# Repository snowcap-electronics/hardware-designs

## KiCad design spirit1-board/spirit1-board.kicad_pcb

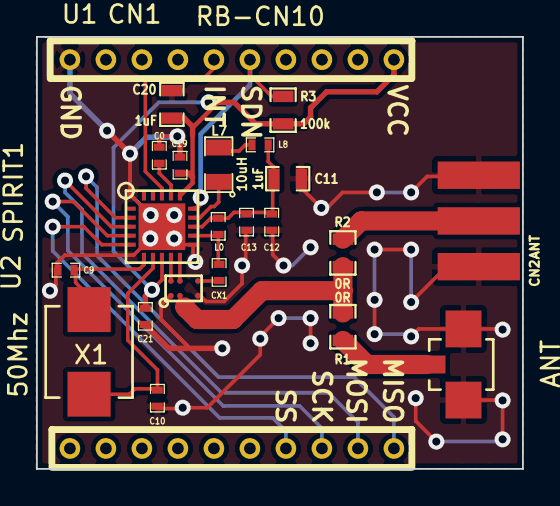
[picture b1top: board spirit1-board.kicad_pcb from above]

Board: 2 copper layers, 27.0 x 24.0 mm, 22 parts (0 on the bottom side), 21 nets.

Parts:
C0, C12: 100nF; SM0402_c
C9: 12pF; SM0402_c
C10: 10pF; SM0402_c
C11, C20: 1uF; SM0603_Capa
C13: 330pF; SM0402_c
C19: 10nF; SM0402_c
C21: 100pF; SM0402_c
CN1: RB-CN10; RB_CN10_2mm
CN2: ANT; RF_SMA
CN3: ANT; U.FL-R-SMT_01
CX1: C; SM0402_c
L0: 150nH; SM0402
L7: 10uH; SM0805
L8: 62nH; SM0402
R1, R2: 0R; SM0603_Resistor
R3: 100k; SM0603_Resistor
U1: SPIRIT1; SPIRIT1_QFN20
U2: BALF-SPI-02D3; BALF_SPI_02D3
X1: 50Mhz; CRYSTAL-ABM3-50.000MHZ-D2Y-F-T

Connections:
/50ohm: R1.2, R2.1, U2.B1
GND: C0.2, C9.2, C10.2, C11.2, C12.2, C13.2, C19.2, C20.2, C21.2, CN1.10, CN2.2, CN3.2, U1.11, U1.21, U2.A1, U2.C1
unnamed: CN1.11, U1.2
unnamed: CN1.12, U1.3
unnamed: CN1.13, U1.4
unnamed: CN1.14, U1.5
unnamed: C0.1, U1.17
unnamed: CN1.5, R3.2, U1.15
unnamed: CN1.6, U1.18
unnamed: CN3.1, R1.1
unnamed: CN2.1, R2.2
unnamed: C11.1, C12.1, C13.1, L0.2, L8.2, U1.13
unnamed: L7.2, L8.1
unnamed: C9.1, U1.6, X1.1
unnamed: C10.1, U1.7, X1.2
unnamed: L7.1, U1.14
unnamed: U1.9, U2.A2
unnamed: U1.10, U2.B2
unnamed: CX1.1, L0.1, U1.12
unnamed: CX1.2, U2.C2
VCC: C19.1, C20.1, C21.1, CN1.1, R3.1, U1.8, U1.16

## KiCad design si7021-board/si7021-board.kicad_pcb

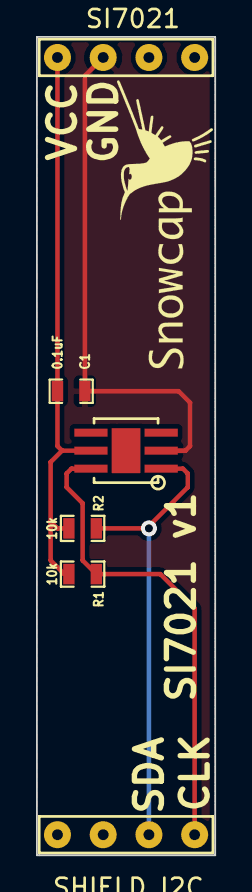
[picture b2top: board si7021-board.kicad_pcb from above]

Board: 2 copper layers, 9.9 x 45.5 mm, 5 parts (0 on the bottom side), 4 nets.

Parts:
C1: 0.1uF; SM0603_Capa
R1, R2: 10k; SM0603_Resistor
U1: SHIELD_I2C
U2: SI7021

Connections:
GND: C1.2, U1.2, U2.2
unnamed: R1.2, U1.8, U2.6
unnamed: R2.2, U1.7, U2.1
VCC: C1.1, R1.1, R2.1, U1.1, U2.5

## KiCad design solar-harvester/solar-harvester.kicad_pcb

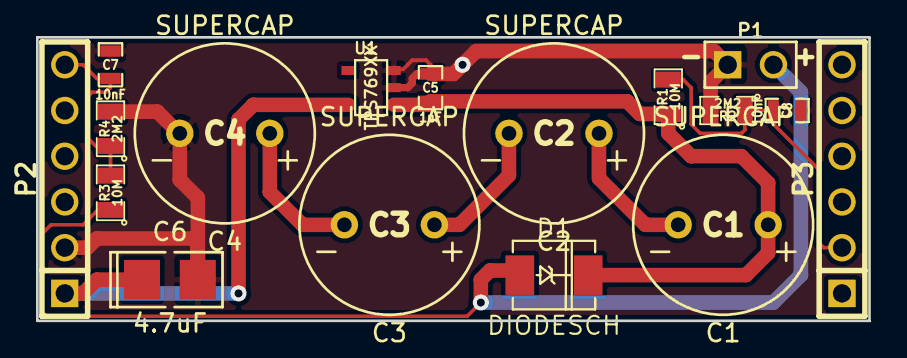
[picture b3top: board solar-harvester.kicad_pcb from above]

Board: 2 copper layers, 46.2 x 15.7 mm, 17 parts (0 on the bottom side), 9 nets.

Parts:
C1, C2, C3, C4: SUPERCAP; SUPERCAP_ESHSR-0010C0-002R7
C5: 1uF; SM0603_Capa
C6: 4.7uF; SM1411_POL
C7, C8: 10nF; SM0603_Capa
D1: DIODESCH; DO-214AC(SMA)
P1: CONN_2; PIN_ARRAY_2X1
P2, P3: CONN_6; PIN_ARRAY-6X1
R1, R3: 10M; SM0805
R2, R4: 2M2; SM0805
U1: TPS769XX; SOT23-5

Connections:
/V_MEASURE1: C7.1, P2.6, R3.2, R4.1
/V_MEASURE2: C8.1, P3.2, R1.2, R2.1
GND: C4.2, C5.2, C6.2, C7.2, C8.2, P1.1, P2.2, R2.2, R4.2, U1.2, U1.3
unnamed: C2.2, C3.1
unnamed: D1.1, P1.2, R3.1
unnamed: C6.1, P2.1, U1.5
unnamed: C1.2, C2.1
unnamed: C1.1, C5.1, D1.2, R1.1, U1.1
unnamed: C3.2, C4.1

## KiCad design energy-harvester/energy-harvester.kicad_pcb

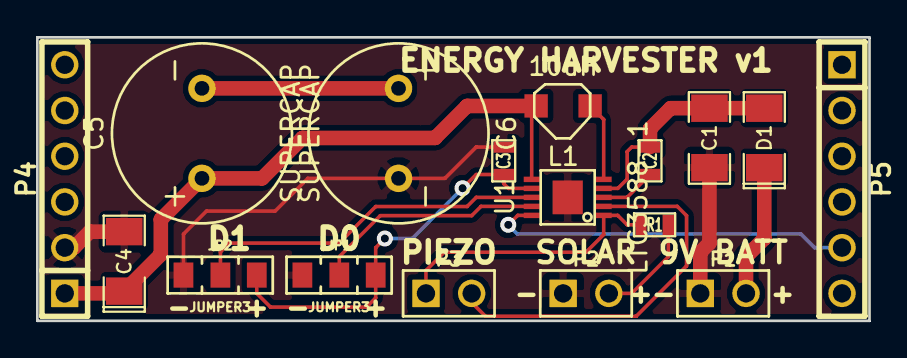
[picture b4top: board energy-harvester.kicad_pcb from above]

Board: 2 copper layers, 46.2 x 15.7 mm, 17 parts (0 on the bottom side), 14 nets.

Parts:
C1: 100uF; SM1206
C2: 1uF; SM0603
C3: 4.7uF; SM0603
C4: 10uF; SM1206POL
C5, C6: SUPERCAP; SUPERCAP_ESHSR-0010C0-002R7
D1: DIODESCH; SM1206POL
JP1, JP2: JUMPER3; SM0805_JUMPER3
L1: 10uH; INDUCTOR-CDRH2D18-LD
P1, P2, P3: CONN_2; PIN_ARRAY_2X1
P4, P5: CONN_6; PIN_ARRAY-6X1
R1: 300R; SM0603
U1: LTC3588-1; LTC3588-1-MSOP10

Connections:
/PGOOD: P5.5, U1.10
/VIN2: C3.1, JP1.3, JP2.3, U1.7
GND: C1.2, C3.2, C4.2, C6.2, JP1.1, JP2.1, P1.1, P2.1, P4.2, U1.11
unnamed: P3.1, R1.2, U1.1
unnamed: P3.2, U1.2
unnamed: JP2.2, U1.8
unnamed: C5.2, C6.1
unnamed: JP1.2, U1.9
unnamed: D1.1, P1.2
unnamed: C2.2, U1.3
unnamed: P2.2, R1.1
unnamed: L1.1, U1.5
unnamed: C1.1, C2.1, D1.2, U1.4
VCC: C4.1, C5.1, L1.2, P4.1, U1.6

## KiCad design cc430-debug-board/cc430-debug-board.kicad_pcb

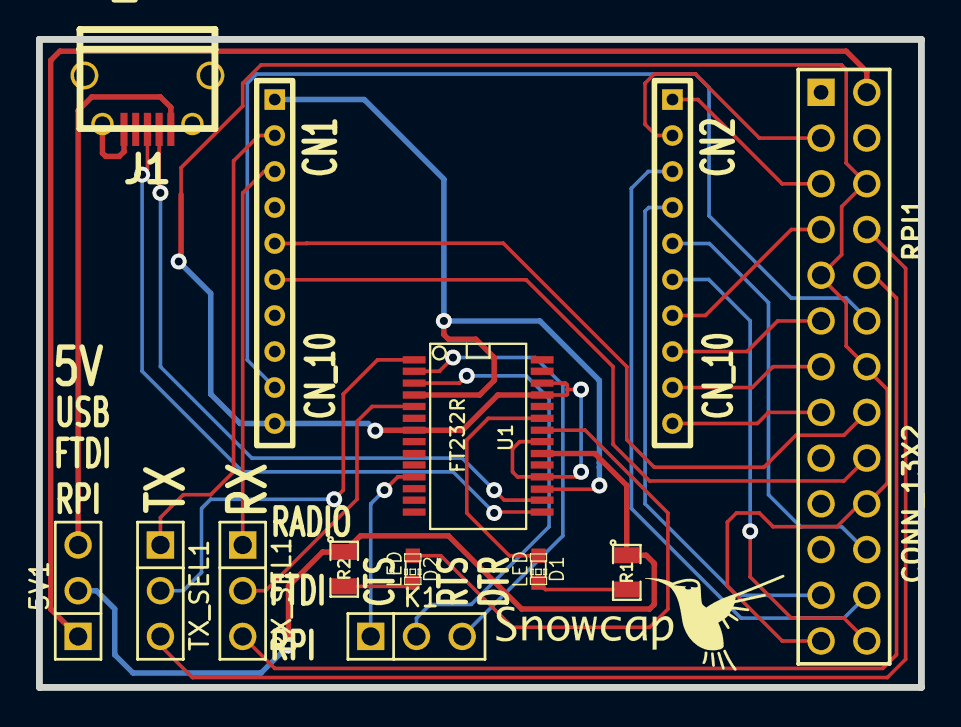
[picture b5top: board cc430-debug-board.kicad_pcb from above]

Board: 2 copper layers, 49.0 x 36.0 mm, 13 parts (0 on the bottom side), 33 nets.

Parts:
5V1: CN_3; PIN_ARRAY_3X1
CN1, CN2: CN_10; CONN-10-2MM
D1, D2: LED; LED-0603
J1: USB_MICRO; USB_MICRO_10118194-0001LF
K1: CONN_3; PIN_ARRAY_3X1
R1, R2: 500R; SM0805
RPI1: CONN_13X2; pin_array_13x2
RX_SEL1: CN_3; PIN_ARRAY_3X1
TX_SEL1: CN_3; PIN_ARRAY_3X1
U1: FT232R; SSOP28

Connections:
+3.3V: CN1.1, U1.4, U1.17
+5V: 5V1.2, R1.1, R2.1, U1.20
/RADIO_A0: CN2.8, RPI1.11
/RADIO_A0_SCLK: CN2.4, RPI1.23
/RADIO_A0_SS: CN2.3, RPI1.24
/RADIO_A1: CN2.9, RPI1.13
/RADIO_A2: CN2.10, RPI1.15
/RADIO_A3: CN1.9, RPI1.12
/RADIO_ACLK: CN2.5, RPI1.22
/RADIO_B0_SCL: CN2.1, RPI1.5
/RADIO_B0_SDA: CN2.2, RPI1.3
/RADIO_NRST: CN1.5, RPI1.16
/RADIO_RFGDO0: CN2.7, RPI1.7
/RADIO_RFGDO2: CN2.6, RPI1.26
/RADIO_RX: CN1.3, RX_SEL1.1
/RADIO_TEST: CN1.6, RPI1.18
/RADIO_TX: CN1.2, TX_SEL1.1
/RPI_RX: RPI1.10, RX_SEL1.3
/RPI_TX: RPI1.8, TX_SEL1.3
GND: CN1.10, J1.5, J1.6, J1.7, J1.8, J1.9, RPI1.6, RPI1.9, RPI1.14, RPI1.20, RPI1.25, U1.7, U1.18, U1.21, U1.25, U1.26
unnamed: RX_SEL1.2, U1.5
unnamed: TX_SEL1.2, U1.1
unnamed: D1.1, U1.23
unnamed: J1.3, U1.15
unnamed: K1.1, U1.11
unnamed: K1.2, U1.3
unnamed: K1.3, U1.2
unnamed: 5V1.1, RPI1.2
unnamed: 5V1.3, J1.1
unnamed: J1.2, U1.16
unnamed: D2.2, R2.2
unnamed: D1.2, R1.2
unnamed: D2.1, U1.22

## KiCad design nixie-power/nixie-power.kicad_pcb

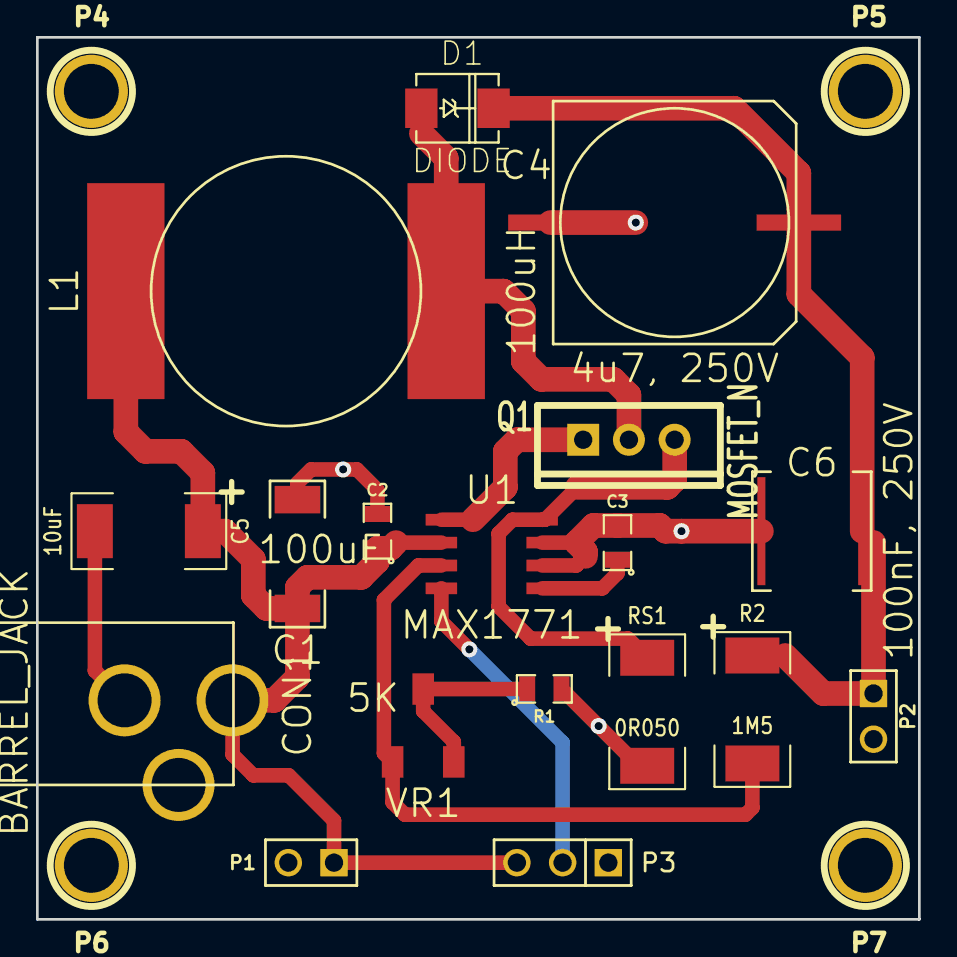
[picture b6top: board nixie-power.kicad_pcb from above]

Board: 2 copper layers, 49.0 x 49.0 mm, 22 parts (0 on the bottom side), 10 nets.

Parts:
C1: 100uF; SM2917
C2, C3: 100nF; SM0805
C4: 4u7, 250V; c_elec_13.5x13.8
C5: 10uF; SM2512
C6: 100nF, 250V; SM2420_fc1
CON1: BARREL_JACK; BARREL_JACK-PJ-002AH
D1: DIODE; DO214
L1: 100uH; UNI-PAC4B
P1, P2: CONN_2; PIN_ARRAY_2X1
P3: CONN_3; PIN_ARRAY_3X1
P4, P5, P6, P7: CONN_1; 1pin
Q1: MOSFET_N; TO220_VERT_GDS
R1: 10K; SM0805
R2: 1M5; SM2512
RS1: 0R050; SM2512
U1: MAX1771; SOIC-8
VR1: 5K; 3314S-TRIMPOT

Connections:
FB: R2.2, U1.3, VR1.1
GND: C1.2, C2.2, C3.2, C4.2, C5.2, C6.2, CON1.2, P1.2, P2.2, P3.1, P4.1, P5.1, P6.1, P7.1, R1.2, RS1.2, U1.6, U1.7
unnamed: C3.1, U1.5
unnamed: C1.1, C2.1, C5.1, CON1.1, L1.1, P1.1, P3.3, U1.2
unnamed: Q1.G, U1.1
unnamed: C4.1, C6.1, D1.2, P2.1, R2.1
unnamed: Q1.S, RS1.1, U1.8
unnamed: P3.2, U1.4
unnamed: D1.1, L1.2, Q1.D
unnamed: R1.1, VR1.2, VR1.3

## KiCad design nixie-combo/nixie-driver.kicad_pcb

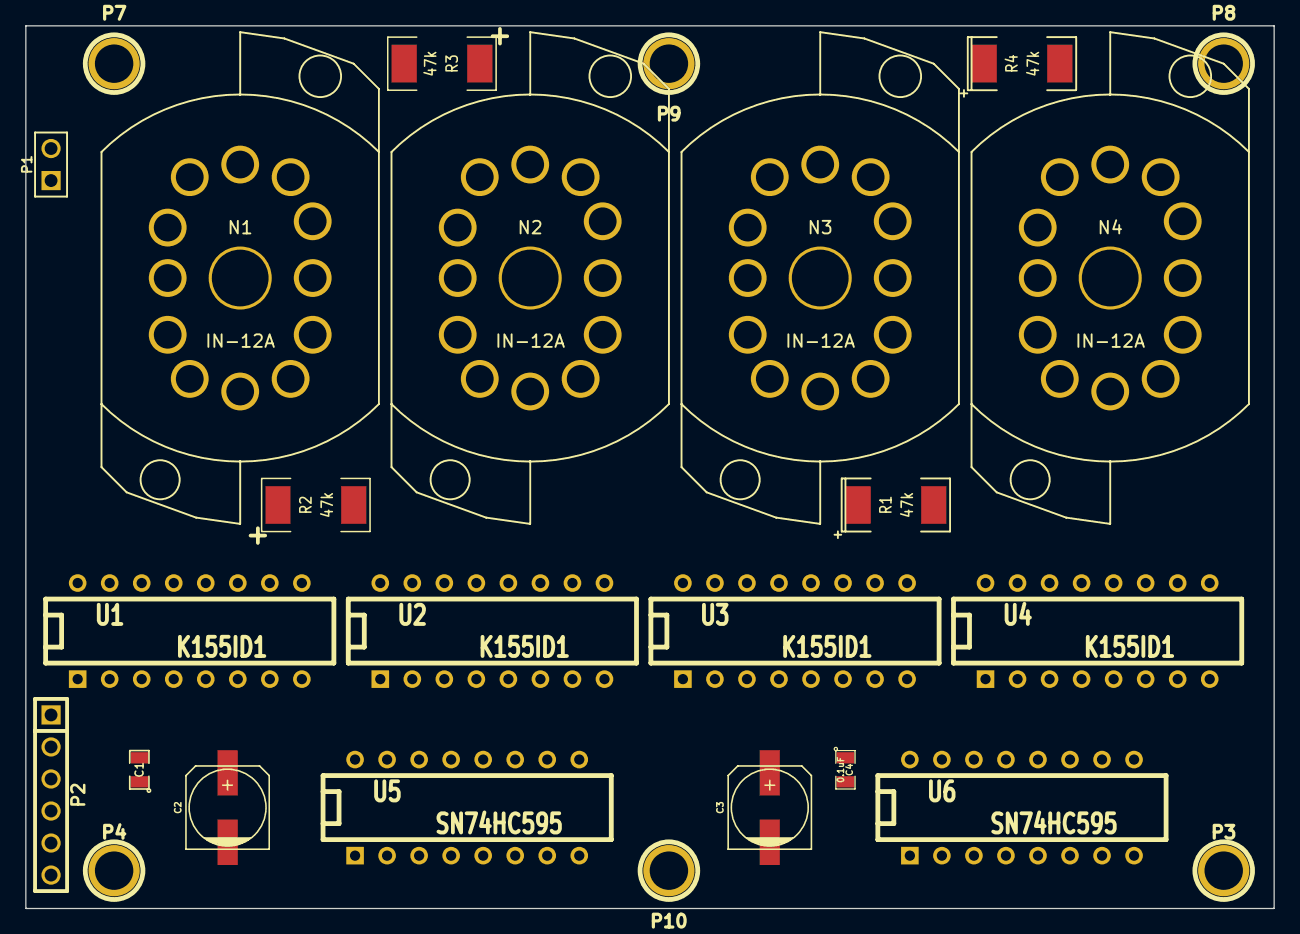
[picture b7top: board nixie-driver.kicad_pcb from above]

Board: 2 copper layers, 99.0 x 70.0 mm, 26 parts (0 on the bottom side), 67 nets, no tracks yet.

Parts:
C1, C4: 0.1uF; SM0805
C2, C3: 100uF; c_elec_6.3x7.7
N1, N2, N3, N4: IN-12A
P1: CONN_2; PIN_ARRAY_2X1
P2: CONN_6; PIN_ARRAY-6X1
P3, P4, P7, P8, P9, P10: CONN_1; 1pin
R1, R2, R3, R4: 47k; SM2512
U1, U2, U3, U4: K155ID1; DIP-16__300
U5, U6: SN74HC595; DIP-16__300

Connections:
+3.3V: C1.1, C2.1, C3.1, C4.1, P2.5, U1.5, U2.5, U3.5, U4.5, U5.10, U5.16, U6.10, U6.16
/a0: N1.2, U1.16
/a1: N1.11, U1.15
/a2: N1.10, U1.8
/a3: N1.9, U1.9
/a4: N1.8, U1.13
/a5: N1.7, U1.14
/a6: N1.6, U1.11
/a7: N1.5, U1.10
/a8: N1.4, U1.1
/a9: N1.3, U1.2
/b0: N2.2, U2.16
/b1: N2.11, U2.15
/b2: N2.10, U2.8
/b3: N2.9, U2.9
/b4: N2.8, U2.13
/b5: N2.7, U2.14
/b6: N2.6, U2.11
/b7: N2.5, U2.10
/b8: N2.4, U2.1
/b9: N2.3, U2.2
/c0: N3.2, U3.16
/c1: N3.11, U3.15
/c2: N3.10, U3.8
/c3: N3.9, U3.9
/c4: N3.8, U3.13
/c5: N3.7, U3.14
/c6: N3.6, U3.11
/c7: N3.5, U3.10
/c8: N3.4, U3.1
/c9: N3.3, U3.2
/d0: N4.2, U4.16
/d1: N4.11, U4.15
/d2: N4.10, U4.8
/d3: N4.9, U4.9
/d4: N4.8, U4.13
/d5: N4.7, U4.14
/d6: N4.6, U4.11
/d7: N4.5, U4.10
/d8: N4.4, U4.1
/d9: N4.3, U4.2
GND: C1.2, C2.2, C3.2, C4.2, P1.1, P2.2, P3.1, P4.1, P7.1, P8.1, P9.1, P10.1, U1.12, U2.12, U3.12, U4.12, U5.8, U5.13, U6.8, U6.13
HT: P1.2, R1.2, R2.2, R3.2, R4.2
unnamed: N4.1, R4.1
unnamed: U4.7, U6.6
unnamed: U4.4, U6.7
unnamed: U4.3, U6.4
unnamed: U3.7, U6.2
unnamed: U3.6, U6.1
unnamed: U3.4, U6.3
unnamed: N1.1, R2.1
unnamed: N2.1, R3.1
unnamed: N3.1, R1.1
unnamed: U3.3, U6.15
unnamed: U4.6, U6.5
unnamed: U5.9, U6.14
unnamed: P2.4, U5.12, U6.12
unnamed: P2.3, U5.11, U6.11
unnamed: P2.1, U5.14
unnamed: U2.4, U5.7
unnamed: U2.7, U5.6
unnamed: U2.6, U5.5
unnamed: U2.3, U5.4
unnamed: U1.4, U5.3
unnamed: U1.7, U5.2
unnamed: U1.6, U5.1
unnamed: U1.3, U5.15

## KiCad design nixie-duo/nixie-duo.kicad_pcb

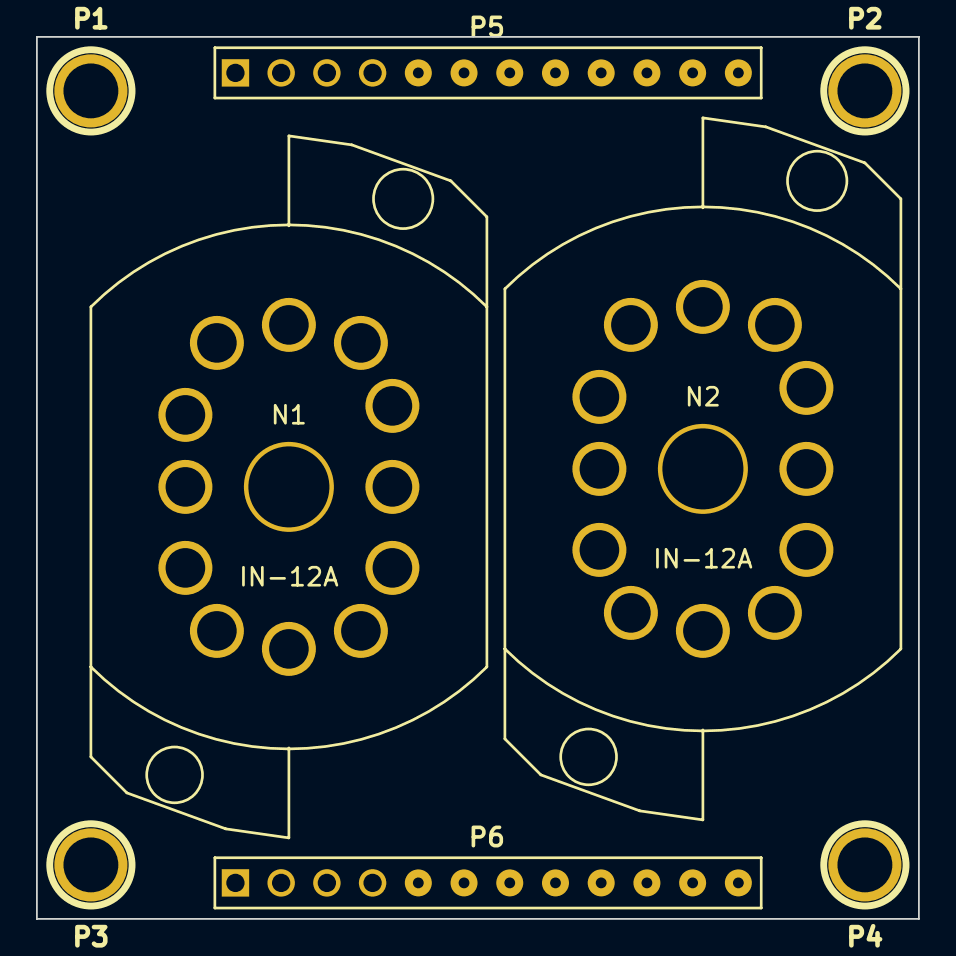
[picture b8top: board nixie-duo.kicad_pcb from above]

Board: 2 copper layers, 49.0 x 49.0 mm, 8 parts (0 on the bottom side), 23 nets, no tracks yet.

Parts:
N1, N2: IN-12A
P1, P2, P3, P4: CONN_1; 1pin
P5, P6: CONN_12; PIN_ARRAY_12x1

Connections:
/A0: N1.2, P5.2
/A1: N1.11, P5.3
/A2: N1.10, P5.11
/A3: N1.9, P5.8
/A4: N1.8, P5.5
/A5: N1.7, P5.4
/A6: N1.6, P5.6
/A7: N1.5, P5.7
/A8: N1.4, P5.9
/A9: N1.3, P5.10
/B0: N2.2, P6.1
/B1: N2.11, P6.2
/B2: N2.10, P6.11
/B3: N2.9, P6.8
/B4: N2.8, P6.4
/B5: N2.7, P6.3
/B6: N2.6, P6.6
/B7: N2.5, P6.7
/B8: N2.4, P6.9
/B9: N2.3, P6.10
GND: P5.12, P6.5
unnamed: N2.1, P6.12
unnamed: N1.1, P5.1

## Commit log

2012-02-07 initial repo, including kicad files and usb-serial board, logo is missing
2012-02-09 added cc430 to snowcap.lib and started the cc430 project
2012-02-10 cc430: fixed cc430 component and added power lines to schema
2012-02-13 cc430: added power components to schema
2012-02-17 cc430: finished first version of schema
2012-02-17 cc430: added spybywire connector to schematic
2012-03-22 cc430: created smd0402 and 48VQFN footprints
2012-03-27 usb-serial: swapped rx-tx pins
2012-03-30 cc430: added board file
2012-03-30 cc430: initial layout on PCB
2012-04-02 cc430: fixed connectors in schema
2012-04-02 cc430: added tmp275 to schema and started PCB
2012-04-03 cc430: PCB work continued, GND planes still missing
2012-04-03 cc430: fixed 3d view
2012-04-03 cc430: almost ready PCB
2012-04-04 cc430: fixed cc430 thermal pad
2012-04-11 cc430: added gnd vias
2012-04-12 usb-serial: added 3v pin, silk needs checking
2012-05-02 rf vcc bug fix and silk polish for production
2012-05-09 cc430: switche rx/tx lines
2012-05-11 cc430: fixed logo kicad: added snowcap logo file
2012-05-11 cc430: connected pins 1,2 and 3 to pinheader
2012-05-16 cc430: added two extra lines for io
2012-05-17 cc430: fixed fill zones
2012-07-24 cc430: Fixed antenna connector SMA GND pads.
2012-07-24 cc430: Defined values (4.7k) for tmp275 pull-up resistors.
2013-03-07 cc430: Added GND for crystal. Updated text to V2.
2013-03-08 cc430: Added reset pull-up.
2013-03-08 Larger pads on cc430 footprint
    Required also some rerouting
2013-03-11 Fixed missing GND thermal pad connection
    -Also Vcc trace width
    -Moved via from capacitor pad
2013-03-13 cc430: Changed the 3D component of R4 to resistor.
2013-07-08 led-board: first version.
2013-07-08 led-board: fixed unconnected trace, added text.
2013-07-10 cc430-debug-board: Initial version.
2013-07-10 cc430-debug-board: changed leds and resistors. Added rough positioning in the board file.
2013-08-29 cc430-debug-board: added routing.
2013-09-26 lsm9ds0: Added component to snowcap library.
2013-09-26 lsm9ds0: Empty schema.
2013-09-27 lsm9ds0: Added initial schema and pcb (wrong footprint for lsm9ds0).
2013-09-28 lib: lsm9ds0: Fixed inputs and outputs.
    Fixed pin directions of the schematic component.
    Added LGA 24 footprint.
2013-09-28 lsm9ds0-board: Initial version.
    Added I2C pull-ups.
    Created PCB.
2013-10-23 lib: stm32f4-64: initial commit.
2013-10-26 lib: lqfp64-longpads: Added footprint.
2013-10-26 mcu-board-stm32f4: Added initial pcb layout.
2013-11-01 lib: Added and updated components.
    Updated:
    * LSM9DS0
    Added:
    * SN65220
    * STM32F4-64
    * USB_MICRO
2013-11-01 mcu-board-stm32f4: Initial version.
    Missing silk screen and checks.
2013-11-07 lib: Added footprint for 25 pin header.
2013-11-07 lib: STM32F4-64: Renamed invalid PB16 to PB15.
2013-11-07 mcu-board-stm32f4: Reverse voltage protection.
    Added FET for reverse voltage protection to 3V line. 5V line is
    assumed to be protected by the regulator.
    Added FET to disconnect the external power pin from the USB VBUS
    sense pin to allow high voltages from the external pin. The TLV70133
    supports up to 24V input.
    Moved crystal capacitors closed to crystal pads.
2013-11-07 mcu-board-stm32f4: Renamed invalid PB16 to PB15.
2013-11-07 mcu-board-stm32f4: Reverse voltage protection.
    Commit the board file as well.
2013-11-07 base-board: Initial schema and pcb layout.
2013-11-08 base-board: Initial PCB.
2013-11-08 Added .gitignore
2013-11-08 base-board: Some addition forgot from the last commit.
2013-11-09 base-board: Added reset and test pins for radio.
2013-11-09 mcu-board-stm32f4: Added a user led.
2013-11-09 logo: Added logos without ref texts.
    Added back and front logos without reference and value texts.
2013-11-09 mcu-board-stm32f4: Add initial silk screen.
2013-11-10 mcu-board-stm32f4: Add version string.
2013-11-10 mcu-board-stm32f4: Add led description.
2013-11-10 mcu-board-stm32f4: Move R2 ref text.
2013-11-11 base-board: Add initial silk screen.
2013-11-12 lsm9ds0-board: Add silk screen.
    Add pin names and the logo to silk screen.
    Prettify some of the trace corners.
2013-11-16 lsm9ds0-board: Increase footprint size for C4.
2013-11-16 lsm9ds0-board: Add gerbers.
2013-11-16 .gitignore: Remove drill files.
2013-11-16 lib: tps70933_dcy: Add schema and footprint.
2013-11-16 mcu-board-stm32f4: Rewrite power regulation.
2013-11-17 base-board: Add gerbers.
2013-11-17 lib: sm0805_breaker: Add silk screen.
2013-11-17 mcu-board-stm32f4: Add breaker labels.
2013-11-17 lib: USB_MICRO: Minor tweaks.
    * Increase pad lenght.
    * Turn oval holes to cirle for proper gerber files.
    * Fix pad 5 position.
2013-11-17 mcu-board-stm32f4: Tweak USB connector footprint.
2013-11-17 mcu-board-stm32f4: Add gerbers.
2013-11-18 Rename gerbers_v1 to gerbers.
2013-12-08 pwm-board: Initial version.
2013-12-08 pwm-board: Add silk screen.
2013-12-15 pwm-board: Add gerbers.
2013-12-28 mcu-board-stm32f4: Add component layout image.
2013-12-30 .gitignore: Add .zip and .png.
2013-12-30 mcu-board-stm32f4: Update component layout image.
2013-12-30 mcu-board-stm32f4: Layout: Correct 22nF to 2.2nF.
2014-01-09 mcu-board-stm32f4: Layout: Update for LM2937.
2014-05-27 nixia-power: Add initial schema for Nixie PS.
2014-05-27 nixie-power: Add LICENCE.
2014-05-29 lib: Add schema for K155ID1, MAX1771, SN74HC595.
2014-05-29 nixie-power: Update something in the .pro file?
2014-05-29 nixie-driver: Add Nixie driver.
2014-05-29 nixie-driver: Replace 5V with 3.3V.
2014-05-29 nixie-power: Correct the power jack.
2014-05-29 lib: Add IN-12A.
2014-05-29 nixie-duo: Initial schema for dual IN-12A.
2014-06-04 lib: Add foot prints.
    Add:
    * 3314S-TRIMPOT
    * BARREL_JACK-PJ-002AH
    * SM2420_fc1
    * SM2917
    * SOIC-8
2014-06-04 nixie-power: Add connector for power switch.
2014-06-04 nixie-power: Add initial pcb layout.
2014-06-12 lib: Add PIN_ARRAY_12x1 and c_elec_13.5x13.8
2014-06-12 nixie-power: Fix C4 foot print. Tune layout.
2014-06-12 nixie-driver: Add initial PCB layout.
2014-06-12 nixie-duo: Add initial PCB layout.
2014-06-12 lib: Add IN-12A foot print.
2014-06-12 nixie-duo: Minor tuning.
2014-06-13 nixie-power: Added initial tracing.
2014-06-14 nixie-power: Save gerber settings.
2014-06-15 nixie-combo: Combine driver and duo boards.
2014-06-16 nixie-combo: Add pcb tracing.
    Rename driver files to combo files.
2014-06-16 nixie-combo: Improved GND plane for nixies.
2014-06-16 nixie-combo: Increase HV clearance to 32mils.
2014-06-16 nixie-power: Increase trace width.
2014-07-10 lib: Add IN-12A-SOCKET.
2014-07-10 nixie-combo: Replace IN-12A with IN-12A-SOCKET.
2014-07-10 nixie-combo: Add silk screen.
2014-07-10 nixie-power: Add silk screen.
2014-07-10 cc430-debug-board: Decrease board size. Use micro USB.
2014-07-10 IN-12A-SOCKET: Increase drill hole to 2.3mm.
2014-07-10 nixie-combo: Use 2.3mm IN-12A-SOCKETs.
2014-07-14 cc430-debug-board: Add RTS/DTR/CTS pins.
2014-07-14 cc430-debug-board: Add gerbers.
2014-07-14 cc430-debug-board: Update GND plane?
2014-07-14 lib: Add LTC3588-1 schematic.
2014-07-14 energy-harvester: Initial schema.
2014-07-15 lib: Add footprints.
    Add:
    - INDUCTOR-CDRH2D18-LD
    - LTC3588-1-MSOP10
    - SM0805_JUMPER3
    - SUPERCAP_ESHSR-0010C0-002R7
2014-07-15 energy-harvester: Fine tune schema. Add initial PCB layout.
2014-07-16 energy-harverster: Add second super cap.
2014-07-18 lib: Add DIODE-1206.
2014-07-18 energy-harvester: Change some components, add logo.
2014-07-19 lib: Add empty snowcap.dcm (newer kicad thing?)
2014-07-19 solar-harvester: Initial buggy schema.
    PCB layout still from energy harvester, need to be rewritten.
2014-07-20 lib: Update snowcap.dcm
2014-07-20 solar-harvester: Correct V_MEASURE1 point.
2014-07-21 lib: Add SM1411_POL.
2014-07-21 solar-harvester: Add initial PCB layout.
2014-07-21 solar-harvester: Add PCB traces.
2014-07-21 solar-harvester: Add gerbers.
2014-07-21 solar-harvester: Update plot parameters.
2014-07-31 lib: Add HSMS-2815 and SOIL_SENSOR_CAPACITIVE.
2014-07-31 soil-moisture-sensor: Add schema, pcb, gerbers.
2014-12-01 RF Board v3
    Johanson Technology balun for cc430 is used instead of one maked with
    discrete components.
    Also antenna schematic component modified to have ground pin and RF_SMA
    footprint matching that.
2014-12-05 Add LED and vias around RF trace
2014-12-05 Add Si7006 humidity and temp sensor
2014-12-05 Fixed again mssing GND from crystal
2014-12-08 Add logo and pin 1 marking for DFN6 component
2014-12-19 Gerbers for RFv3
2014-12-19 Add top paste lauer to gerbers
2014-12-19 lib: Clean old logos away, add half-sized version
2014-12-19 flashsnap: Introduce C-trigger and M-trigger of the Flashsnap project
    Ordered from OSH Park on 18.12.2014
2014-12-19 Fix for un-connected pin 28 on cc430
2014-12-19 Update RBv3 gerbers
2014-12-19 Connect unconnected +3.3v islands together
    Also again missing GND from crystal
2014-12-19 Updated gerber files
2015-09-27 lib: Add spirit1 and balf-spi-02d3
2015-09-27 spirit1: Add initial spirit1 schema
2015-09-28 lib: Add RB-CN10 BALF_SPI_02D3 SPIRIT1_QFN20
2015-09-28 spirit1-board: Add pcb without any traces
2015-10-18 lib: Add new footprints
    Add:
    * CRYSTAL-ABM3-50.000MHZ-D2Y-F-T
    * RB_CN10_2mm
    * U.FL-R-SMT_01
2015-10-18 spirit1: Finalise schema and pcb
2015-10-18 lib: Add SHIELD_I2C and SI7021
2015-10-18 si7021: Add si7021 board
2015-10-25 si7021: Add silk screen pin1 ID
2015-10-25 si7021: Add pin names to silk screen
    Fix annotation.
2015-10-25 si7021: Add Gerbers
2015-10-25 spirit1: Add silk screen
2015-10-25 spirit1: Add gerbers
2015-10-31 spirit: Add SDN pull-up
    Fix some component sizes.
2015-10-31 spirit1: Add power decoupling caps.
2015-11-08 si7021: Hide extra markings from the gerbers
2015-11-08 spirit1: Hide extra markings from the gerbers
2016-02-21 lib: Add SPSGRF, fix RB_CN10_2mm (22mm width)
2016-02-21 spsgrf: Add SPIRIT1 based SPSGRF radio board
